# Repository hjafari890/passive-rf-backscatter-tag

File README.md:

# Single-Sided FR-4 Passive RF Backscatter Tag System

An open-source, production-ready research platform for **single-sided, zero-via passive RF backscatter tags** milled on standard 1.6 mm FR-4. The repository packages complete KiCad 9.0 hardware projects, ready-to-mill CAM/Gerber manufacturing packages, an interactive Python Tkinter/Matplotlib real-time SDR acquisition GUI, GNU Radio Companion DSP flowgraphs, electrodynamic simulation solvers, and experimental validation reports.

---

## 📸 System Gallery

| Fabricated Tag Prototypes (Milled Single-Sided FR-4) | Physical Testing Setup (NI USRP-2900 + Tags) |
| :---: | :---: |
|  |  |

| Real-Time Python SDR Dashboard | GNU Radio Vector Phase Constellation |
| :---: | :---: |
|  |  |

---

## ⚡ Operating Principle: Harrington Loaded-Scatterer Theory

The tag modulates incident radio-frequency illumination without an active transmitter or battery. According to **Harrington's theory of loaded scatterers**, terminating an antenna with complex load impedance $Z_L = R_L + j X_L$ controls its reradiated field:

$$\sigma(Z_L) = \left| \sqrt{\sigma_{\text{str}}} - \frac{\lambda}{\sqrt{4\pi}} \frac{R_a}{Z_a + Z_L} \cdot \tilde{g} \right|^2$$

where $\sigma_{\text{str}}$ is the tag's structural radar cross section (metal shape reflection), $Z_a = R_a + j X_a \approx 50\,\Omega$ is the antenna input impedance, $\lambda$ is wavelength, and $\tilde{g}$ is the vector gain pattern.

Each prototype features an on-board 3-pin $2.54\,\text{mm}$ header (`J1`) enabling **3 distinct physical modulation states**:

| State | Physical Termination | Impedance ($Z_L$) | Reflection ($\Gamma$) | RF Physical Action | Constellation Behavior |
| :---: | :---: | :---: | :---: | :---: | :---: |
| **State 1** | $50\,\Omega$ SMD 0805 Resistor | $50\,\Omega$ | $\Gamma \approx 0$ | **Absorb:** Energy dissipates in resistor; minimum backscatter | Constellation origin ($0, 0$) |
| **State 2** | Direct GND short jumper | $0\,\Omega$ | $\Gamma \approx -1 \angle 180^\circ$ | **Reflect:** Full reflection with $180^\circ$ phase inversion | Left phase plane quadrant |
| **State 3** | Open circuit (unconnected) | $\infty\,\Omega$ | $\Gamma \approx +1 \angle 0^\circ$ | **Reflect:** Full reflection in-phase ($0^\circ$) | Right phase plane quadrant |

The differential radar cross section ($\Delta \sigma$) between absorb and reflect is:
$$\Delta \sigma = \frac{\lambda^2}{4\pi} G_a^2 |\Gamma_1 - \Gamma_2|^2$$
Yielding a theoretical $\approx 6\,\text{dB}$ power delta for Absorb vs. Reflect ($|\Delta \Gamma| \approx 1.0$), and a $180^\circ$ phase plane flip for Open vs. Short ($|\Delta \Gamma| = 2.0$).

---

## 🏷️ Fabricated Tag Prototypes & CNC Milling Specifications

All boards are engineered specifically for **single-sided CNC isolation milling** (LPKF ProtoMat or 3018 CNC) with zero plated through-holes:
- **Substrate:** Standard 1.6 mm FR-4 ($\varepsilon_r = 4.4$, $\tan\delta = 0.02$).
- **Copper Foil:** $35\,\mu\text{m}$ (1 oz) single-sided top layer (`F.Cu`), zero vias.
- **Milling Tool:** $0.40\,\text{mm}$ isolation bit with $\ge 0.50\,\text{mm}$ safety clearance and $\ge 0.50\,\text{mm}$ minimum trace width.
- **RF Feedline:** Coplanar Waveguide with Ground (CPWG) with trace width $W = 1.85\,\text{mm}$ and ground gap $G = 0.50\,\text{mm}$ achieving characteristic impedance $Z_0 = 49.0\,\Omega$.

| Parameter | Board 1: 2.44 GHz IFA Tag | Board 2: Sub-1GHz Meander Tag | Board 3: Leggiero Cavity Bowtie Tag |
| :--- | :--- | :--- | :--- |
| **Primary CAD** |  |  |  |
| **Operating Frequency** | $2.440\,\text{GHz}$ (ISM / Wi-Fi) | $868 / 915\,\text{MHz}$ (IoT / RFID) | $2.437\,\text{GHz}$ (Wi-Fi Ch 6) |
| **Antenna Geometry** | Planar Inverted-F (TI SWRA117D derived) | Single-Sided Meander Monopole | Radial Cavity Bowtie Aperture ($80^\circ$ sector) |
| **Board Footprint** | $45.0 \times 35.0\,\text{mm}$ | $45.0 \times 38.0\,\text{mm}$ | $60.0 \times 55.0\,\text{mm}$ |
| **Antenna Envelope** | $15.2 \times 5.7\,\text{mm}$ | $34.0 \times 16.0\,\text{mm}$ ($L_{\text{eff}}=73.5\,\text{mm}$) | $36.0 \times 15.5\,\text{mm}$ (Cavity aperture) |
| **Simulated Gain ($G_a$)**| $+2.1\,\text{dBi}$ | $+0.8\,\text{dBi}$ | $+4.2\,\text{dBi}$ |
| **Return Loss ($S_{11}$)**| $-24.4\,\text{dB}$ | $-19.2\,\text{dB}$ | $-18.6\,\text{dB}$ (Wideband) |
| **Diff. RCS ($\Delta \sigma$)** | $-26.5\,\text{dBsm}$ ($0.0022\,\text{m}^2$) | $-21.8\,\text{dBsm}$ ($0.0066\,\text{m}^2$) | $-22.5\,\text{dBsm}$ ($0.0056\,\text{m}^2$) |
| **Key Advantage** | Compact, standard $50\,\Omega$ IFA | Sub-1GHz zero-via replacement | High forward gain, body proximity shield |
| **Hardware Project** | [`hardware/board1_ifa_2.4ghz/`](hardware/board1_ifa_2.4ghz/) | [`hardware/board2_meander_sub1ghz/`](hardware/board2_meander_sub1ghz/) | [`hardware/board3_cavity_bowtie_2.4ghz/`](hardware/board3_cavity_bowtie_2.4ghz/) |

---

## 📁 Repository Structure

```text
passive-rf-backscatter-tag/
├── hardware/                         # KiCad 9 hardware projects & CAM milling files
│   ├── board1_ifa_2.4ghz/            # Board 1 IFA project, Gerbers, DXF, DRC reports
│   ├── board2_meander_sub1ghz/       # Board 2 Meander Sub-1GHz project & CAM package
│   ├── board3_cavity_bowtie_2.4ghz/  # Board 3 Cavity Bowtie project & CAM package
│   └── scripts/                      # Automated KiCad build & export scripts
│
├── software/                         # Real-time SDR acquisition & detection software
│   ├── backscatter_gui_app.py        # Primary Tkinter + Matplotlib real-time GUI (>300 FPS)
│   ├── mock_usrp.py                  # Physics-grounded synthetic SDR generator
│   ├── sdr_worker.py                 # Multi-threaded UHD / mock acquisition pipeline
│   ├── backscatter_metrics.py        # SCNR, moving average, and centroid algorithms
│   ├── plot_backscatter_results.py   # Offline capture analysis and publication figures
│   └── gnuradio/                     # GNU Radio DSP flowgraphs (.grc and .py)
│
├── simulation/                       # Electrodynamic solvers & mathematical models
│   ├── antenna_models.py             # Analytical models for IFA, Meander, and Bowtie
│   ├── rcs_simulation.py             # Harrington radar cross section solver
│   ├── calc_feedline_impedance.py    # Analytical CPWG 50-Ohm feedline impedance solver
│   ├── calc_meander_dims.py          # Sub-1GHz trace length & meander calculator
│   └── simulate_all.py               # Master sweep script generating S11 & Smith charts
│
├── docs/                             # Academic reports, walkthroughs & visual assets
│   ├── assets/                       # High-resolution photos, captures, & plots
│   ├── hardware_walkthrough.md       # Board fabrication & assembly guide
│   ├── simulation_report.md          # Numerical validation & impedance curves
│   └── software_architecture.md     # SDR architecture & threading model
│
├── tests/                            # Automated pytest verification test suite
│   ├── test_hardware_integrity.py    # DRC, Gerber, and CAM compliance tests
│   ├── test_simulation_models.py     # Antenna modeling and Harrington solver tests
│   └── test_software_mock.py         # SDR mock streaming and GUI lifecycle tests
│
├── launch_backscatter_gui.bat        # 1-Click launcher for SDR GUI Dashboard
├── launch_gnuradio_gui.bat           # 1-Click launcher for GNU Radio QT detector
├── open_gnuradio_companion.bat       # 1-Click launcher for GNU Radio flowgraph editor
├── load_backscatter_data.m           # MATLAB script for publication figure generation
├── requirements.txt                  # Python dependencies
└── README.md                         # This file
```

---

## 🚀 Quick Start Guide

### 1. Prerequisites
- **Python:** 3.9+ with `numpy`, `scipy`, `matplotlib` (install via `pip install -r requirements.txt`).
- **SDR Hardware (Optional):** NI USRP-2900 or Ettus B200 via USB 3.0.
  * *If no SDR hardware is detected, the software automatically transitions to physics-grounded mock streaming without errors.*

### 2. Launching the SDR Acquisition Dashboard

- **Windows 1-Click:** Double-click [`launch_backscatter_gui.bat`](launch_backscatter_gui.bat)
- **Command Line (Live Hardware / Auto-Detect):**
  ```bash
  python software/backscatter_gui_app.py
  ```
- **Command Line (Force Offline Mock Streaming):**
  ```bash
  python software/backscatter_gui_app.py --mock
  ```

### 3. Launching GNU Radio DSP Flowgraph

- **Windows 1-Click:** Double-click [`launch_gnuradio_gui.bat`](launch_gnuradio_gui.bat)
- **Visual GRC Editor:** Double-click [`open_gnuradio_companion.bat`](open_gnuradio_companion.bat)
- **Command Line:**
  ```bash
  python software/gnuradio/backscatter_detector_gnuradio.py
  ```

### 4. Running Electrodynamics Simulations

Execute the electrodynamics engine to recompute $S_{11}$, differential RCS, and Smith chart trajectories:
```bash
python simulation/simulate_all.py
```

### 5. Running Automated Verification Tests

```bash
pytest tests/ -v
```

---

## 🔬 Experimental Findings & Practical Engineering Notes

Fabricating and testing passive backscatter tags in an unshielded lab environment revealed critical insights:

1. **Carrier Leakage vs. Manual Jumper Modulation:**
   - **Direct-Current Carrier Overload:** Because tag modulation operates at the exact incident carrier frequency ($f_c = 2.44\,\text{GHz}$) without a frequency-shifting subcarrier (e.g., no active RF oscillator or MCU clocking an RF switch), the receiver observes the backscatter step directly on top of massive Line-of-Sight (LoS) carrier leakage and static reflections from lab desks, walls, and monitors.
   - **Small Signal over Large Carrier:** The tag reflection represents a tiny millivolt delta superimposed on a massive direct carrier wave.
   - **Manual Jumper Limitations:** Changing physical jumpers introduces human-body hand capacitance and multipath shifts that dwarf the tag's backscatter step. This proved that static DC backscattering with manual jumpers is exceptionally sensitive to environment movements.

2. **DC Step Detection & Receiver Dynamic Range:**
   - In direct-conversion SDR front-ends (AD9361 / USRP B200), hardware DC-offset tracking loops interpret static backscatter state transitions as DC drift and notch them out.
   - **Solution:** Software-defined carrier leakage cancellation via the **Auto-Zero Baseline** button captures a 1-second background snapshot and translates the complex constellation centroid to origin $(0, 0)$.

3. **GNU Radio vs. Python Tkinter Dashboard:**
   - **GNU Radio:** Hardware-accelerated Qt vector sinks and native C++ DSP blocks provide instant, jitter-free observation of phase flips in the IQ plane, making tiny tag reflections distinguishable.
   - **Python GUI:** Provides higher-level engineering automation (instant MATLAB `.mat` export, auto-zeroing, live SCNR calculation, and time-domain power logging).

4. **Human Body Proximity & Ground Border (Board 3):**
   - The cavity ground shield on Board 3 (Leggiero Bowtie) acts as a reflector and RF return path, significantly dampening parasitic detuning when operated near human tissue compared to ground-isolated dipoles.

---

## 📜 License & Citation

This project is licensed under the **MIT License** — see the [LICENSE](LICENSE) file for details.

If you use these tag designs, simulation models, or SDR acquisition tools in your research, please cite:
```bibtex
@misc{jafari2026passivebackscatter,
  author = {Hassan Jafari},
  title = {Single-Sided FR-4 Passive RF Backscatter Tag System: Hardware, SDR Software, and Electrodynamic Modeling},
  year = {2026},
  publisher = {GitHub},
  howpublished = {\url{https://github.com/hjafari890/passive-rf-backscatter-tag}}
}
```

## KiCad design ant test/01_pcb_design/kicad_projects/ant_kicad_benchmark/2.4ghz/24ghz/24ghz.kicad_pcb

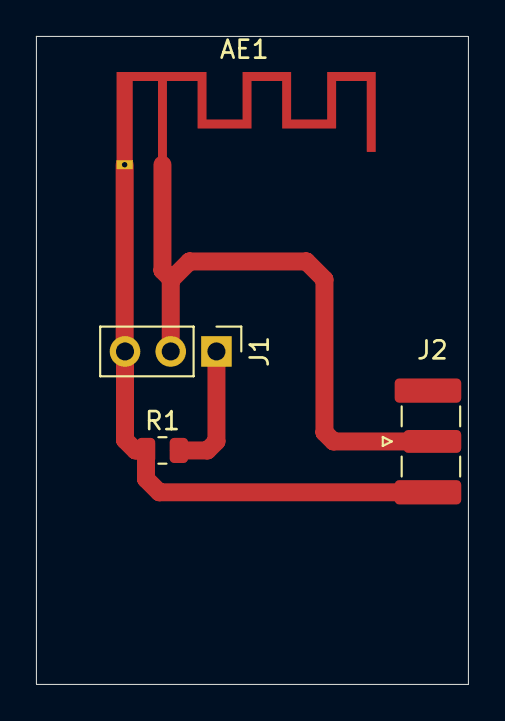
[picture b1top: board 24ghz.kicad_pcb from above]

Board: 2 copper layers, 24.0 x 36.0 mm, 4 parts (0 on the bottom side), 3 nets.

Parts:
AE1: Antenna_Shield; Texas_SWRA117D_2.4GHz_Right
J1: Conn_01x03; PinHeader_1x03_P2.54mm_Vertical
J2: Conn_Coaxial; SMA_Samtec_SMA-J-P-H-ST-EM1_EdgeMount
R1: 50; R_0805_2012Metric

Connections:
GND: AE1.2 (Shield), J1.3, J2.2 (Ext), R1.1
unnamed: AE1.1 (A), J1.2, J2.1 (In)
unnamed: J1.1, R1.2

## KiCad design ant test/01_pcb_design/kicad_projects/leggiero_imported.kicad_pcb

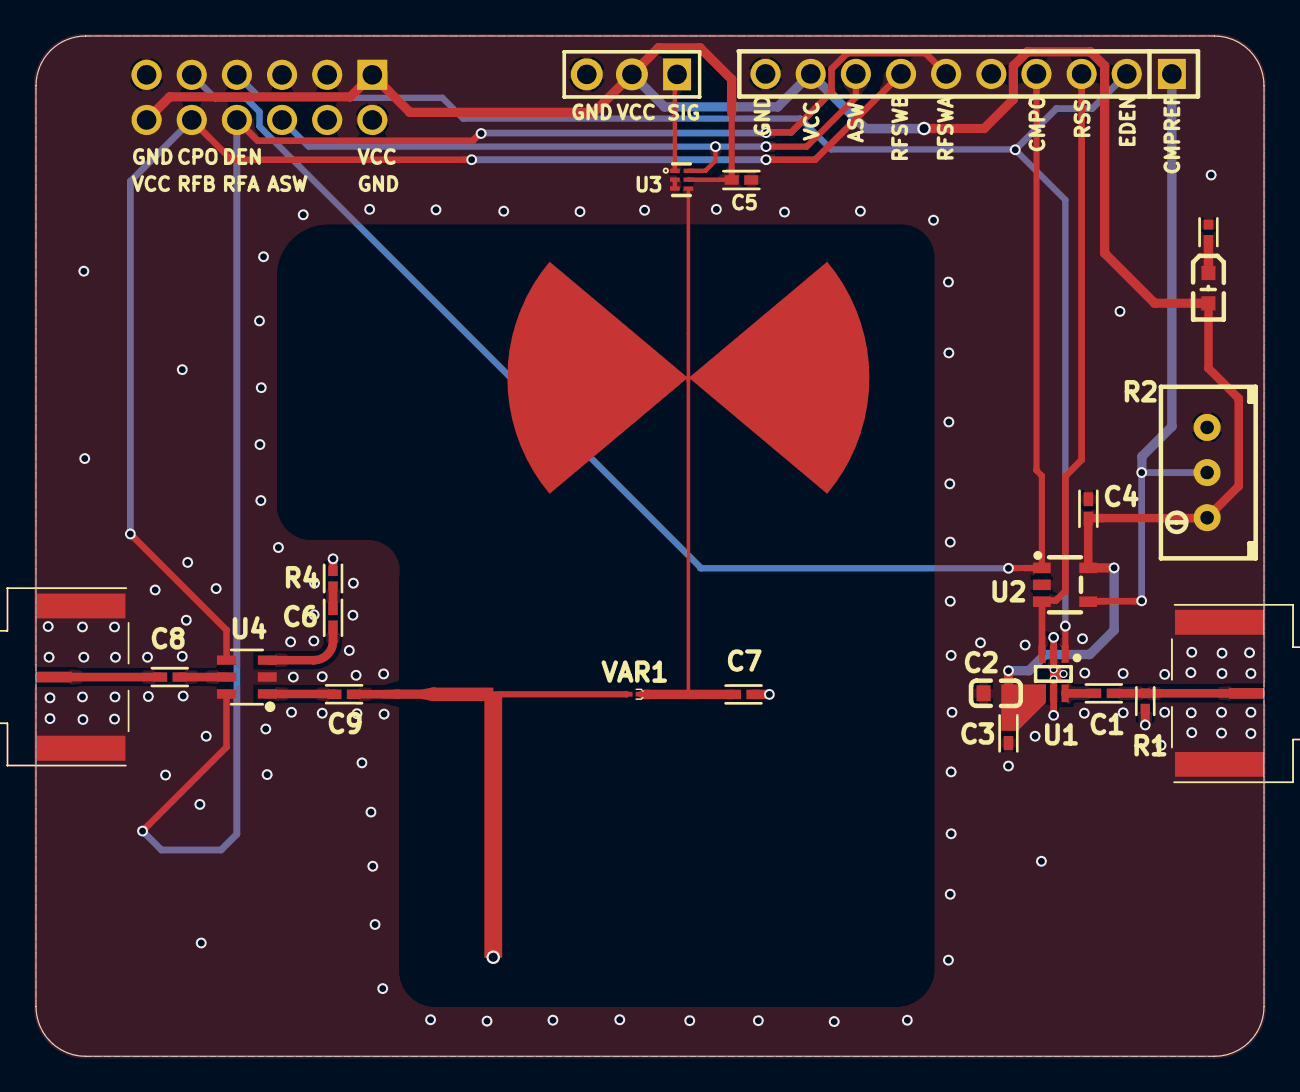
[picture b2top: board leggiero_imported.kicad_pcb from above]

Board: 4 copper layers, 69.1 x 57.4 mm, 24 parts (1 on the bottom side), 19 nets.

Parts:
C1: 1nF; C0402
C2: 100pF; C0603
C3, C4, C5: 0.1uF; C0402
C6, C8, C9: 27pF; C0402
C7: 20pF; C0402
J1: Header1x10P
J2: Header2x6P
J3: Header1x3P
LED1: LED; LED0603
R1: 47Ohm; R0402
R2: 3296W-1-103LF
R3: 1kOhm; R0402
R4: 49.9Ohm; R0402
SMA1, SMA2: RF2203017
U1: LT5534ESC6; LT5534ESC6#TRPBF
U2: TLV3201AIDBVR
U3: XS3A1T3157GMX; XSON6_115
U4: HMC221BE; SOT-23-6
VAR1: MAVR-000120; D0201

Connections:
ASIG: J3.1, U3.1
ASWSEL: J1.8, J2.6, U3.6
CMPOUT: J1.4, J2.9, U2.1
CMPREF: J1.1, R2.2, U2.4
EDEN: J1.2, J2.7, U1.1
GND: C2.1, C3.1, C4.1, C5.2, C7.2, C9.2, J1.10, J2.2, J2.11, J3.3, R1.1, R2.3, R3.1, R4.1, SMA1.2, SMA1.3, SMA1.4, SMA1.5, SMA2.2, SMA2.3, SMA2.4, SMA2.5, U1.2, U1.5, U2.2, U3.2, U3.3, U4.2, VAR1.2
NetC1_1: C1.1, U1.6
NetC1_2: C1.2, R1.2, SMA1.1
NetC6_1: C6.1, U4.3
NetC6_2: C6.2, R4.2
NetC7_1: C7.1, U3.4, VAR1.1
NetC8_1: C8.1, SMA2.1
NetC8_2: C8.2, U4.5
NetC9_1: C9.1, U4.1
NetLED1_2: LED1.2, R3.2
RFSWA: J1.6, J2.8, U4.6
RFSWB: J1.7, J2.10, U4.4
RSS: J1.3, U1.3, U2.3
VCC_3V3: C2.2, C3.2, C4.2, C5.1, J1.9, J2.1, J2.12, J3.2, LED1.1, R2.1, U1.4, U2.5, U3.5

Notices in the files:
README.md:
License: MIT
